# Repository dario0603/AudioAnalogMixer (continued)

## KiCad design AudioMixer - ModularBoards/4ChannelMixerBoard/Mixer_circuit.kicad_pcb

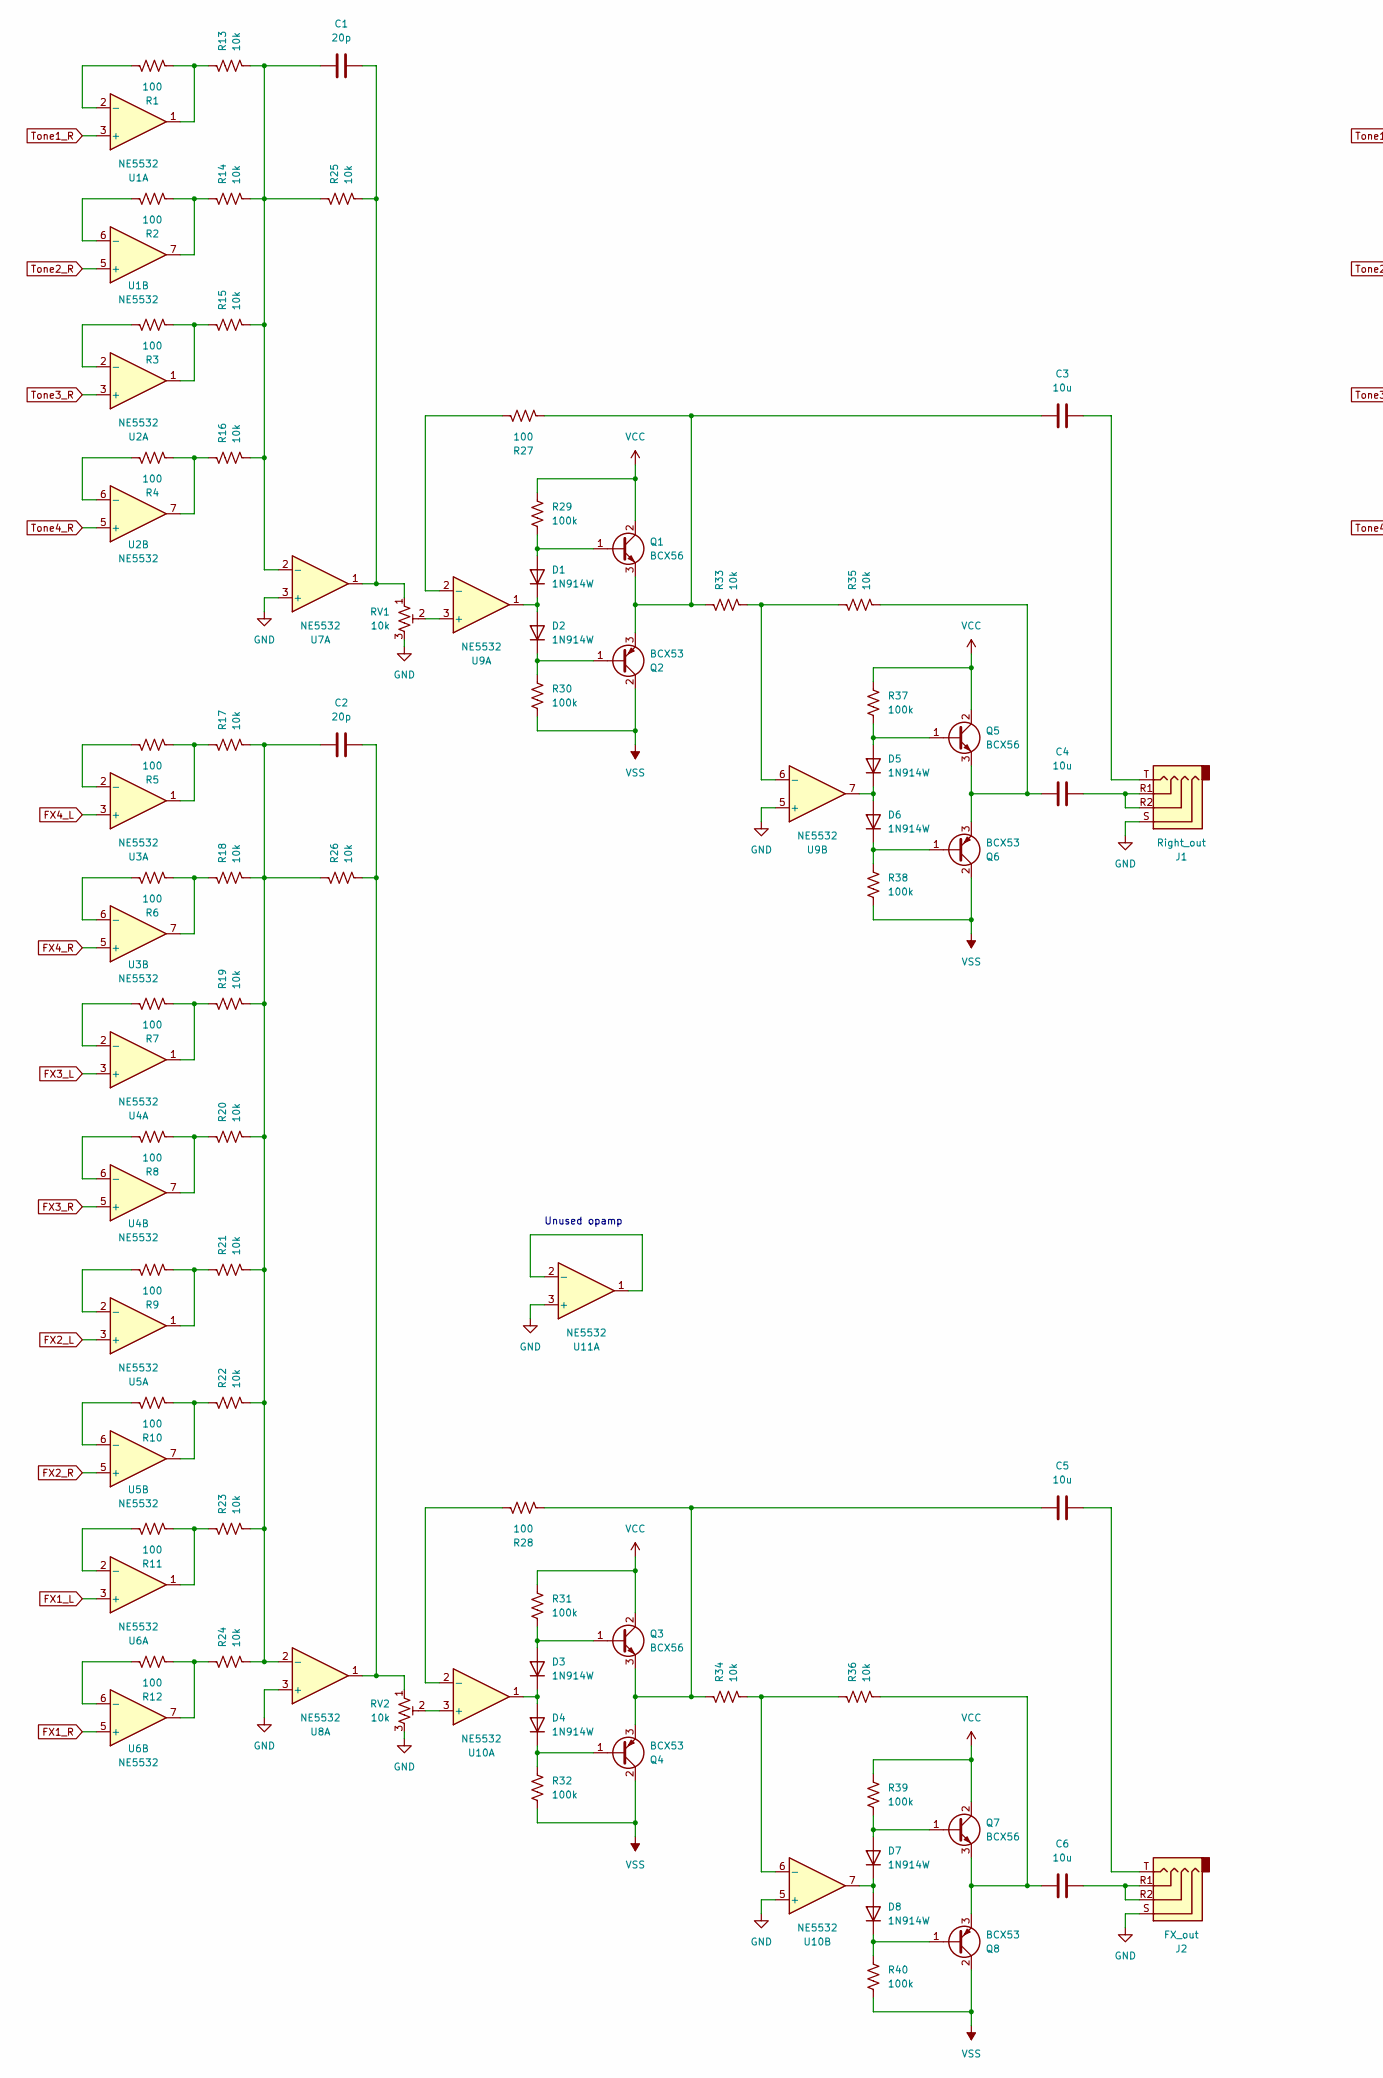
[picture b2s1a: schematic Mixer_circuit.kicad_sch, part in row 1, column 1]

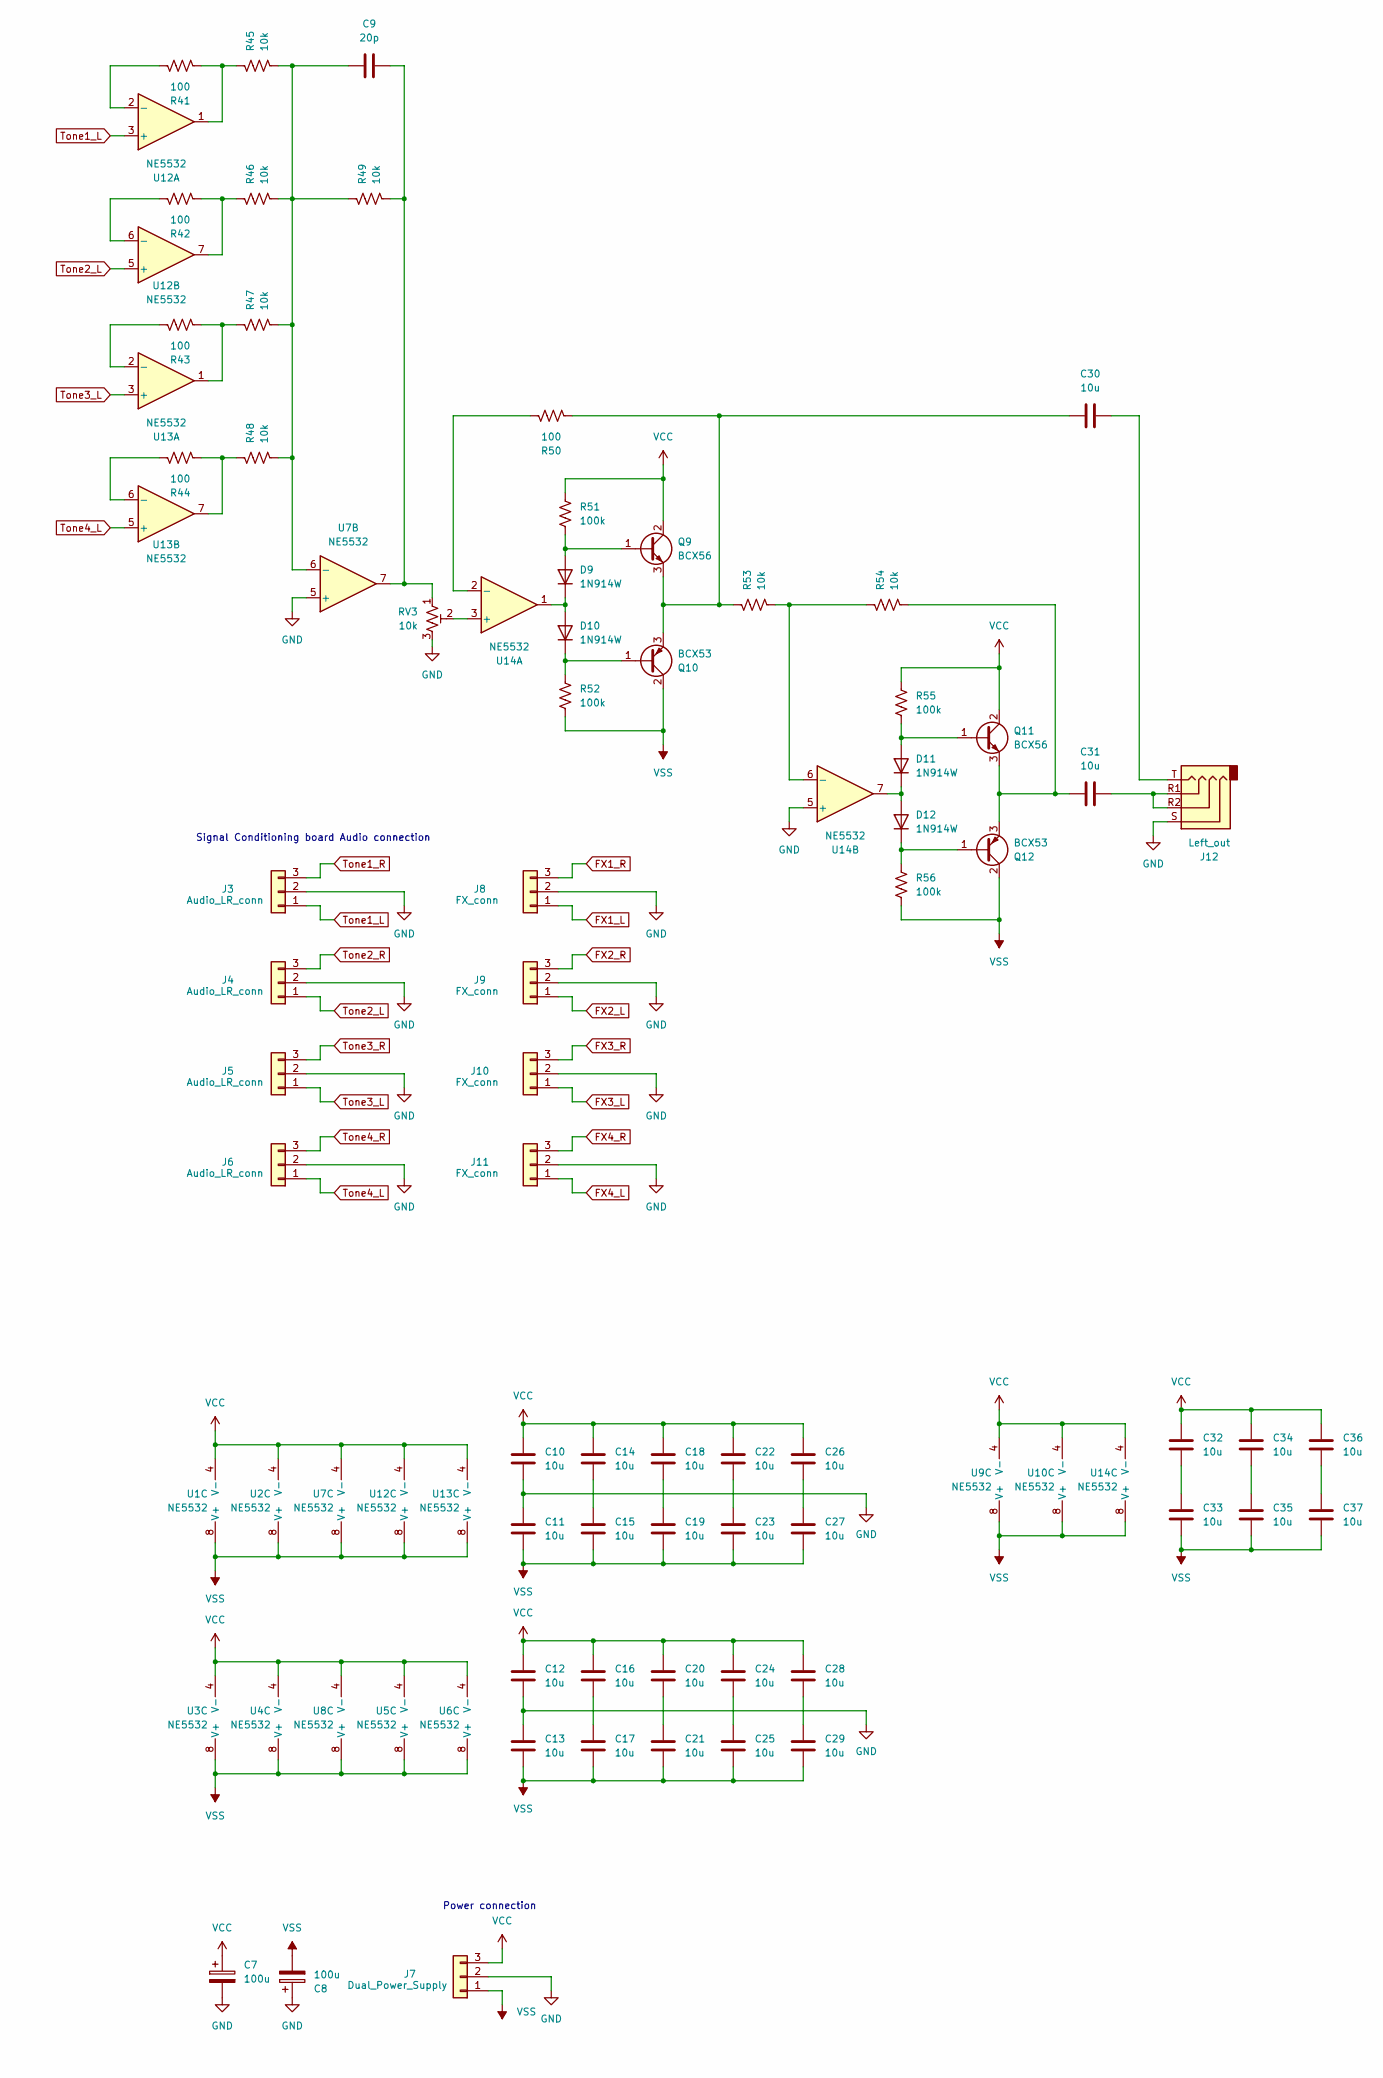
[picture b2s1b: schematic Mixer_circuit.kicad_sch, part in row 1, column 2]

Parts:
C1, C2, C9: 20p; C_0603_1608Metric_Pad1.08x0.95mm_HandSolder
C3, C4, C5, C6, C10, C11, C12, C13, C14, C15, C16, C17, C18, C19, C20, C21, C22, C23, C24, C25, C26, C27, C28, C29, C30, C31, C32, C33, C34, C35, C36, C37: 10u; C_1206_3216Metric_Pad1.33x1.80mm_HandSolder
C7, C8: 100u; CP_Elec_10x10.5
D1, D2, D3, D4, D5, D6, D7, D8, D9, D10, D11, D12: 1N914W; D_SOD-123
J1: Right_out; Jack_3.5mm_PJ320E_Horizontal
J2: FX_out; Jack_3.5mm_PJ320E_Horizontal
J3, J4, J5, J6: Audio_LR_conn; PinHeader_1x03_P2.54mm_Vertical
J7: Dual_Power_Supply; PinHeader_1x03_P2.54mm_Vertical
J8, J9, J10, J11: FX_conn; PinHeader_1x03_P2.54mm_Vertical
J12: Left_out; Jack_3.5mm_PJ320E_Horizontal
Q1, Q3, Q5, Q7, Q9, Q11: BCX56; SOT-89-3
Q2, Q4, Q6, Q8, Q10, Q12: BCX53; SOT-89-3
R1, R2, R3, R4, R5, R6, R7, R8, R9, R10, R11, R12, R27, R28, R41, R42, R43, R44, R50: 100; R_0603_1608Metric_Pad0.98x0.95mm_HandSolder
R13, R14, R15, R16, R17, R18, R19, R20, R21, R22, R23, R24, R25, R26, R33, R34, R35, R36, R45, R46, R47, R48, R49, R53, R54: 10k; R_0603_1608Metric_Pad0.98x0.95mm_HandSolder
R29, R30, R31, R32, R37, R38, R39, R40, R51, R52, R55, R56: 100k; R_0603_1608Metric_Pad0.98x0.95mm_HandSolder
RV1, RV2, RV3: 10k; Potentiometer_Alps_RK097_Single_Horizontal
U1, U2, U3, U4, U5, U6, U7, U8, U9, U10, U11, U12, U13, U14: NE5532; SOIC-8_3.9x4.9mm_P1.27mm

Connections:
FX1_L: J8.1, U6.3 (+)
FX1_R: J8.3, U6.5 (+)
FX2_L: J9.1, U5.3 (+)
FX2_R: J9.3, U5.5 (+)
FX3_L: J10.1, U4.3 (+)
FX3_R: J10.3, U4.5 (+)
FX4_L: J11.1, U3.3 (+)
FX4_R: J11.3, U3.5 (+)
GND: C7.2, C8.1, C10.1, C11.2, C12.1, C13.2, J1.S, J2.S, J3.2, J4.2, J5.2, J6.2, J7.2, J8.2, J9.2, J10.2, J11.2, J12.S, RV1.3, RV2.3, RV3.3, U7.3 (+), U7.5 (+), U8.3 (+), U9.5 (+), U10.5 (+), U11.3 (+), U14.5 (+)
unnamed: C1.2, R25.2, RV1.1, U7.1
unnamed: C2.2, R26.2, RV2.1, U8.1
unnamed: C3.2, J1.T
unnamed: C4.2, J1.R1, J1.R2
unnamed: C5.2, J2.T
unnamed: C6.2, J2.R1, J2.R2
unnamed: C9.2, R49.2, RV3.1, U7.7
unnamed: C14.1, C15.2
unnamed: C16.1, C17.2
unnamed: C18.1, C19.2
unnamed: C20.1, C21.2
unnamed: C22.1, C23.2
unnamed: C24.1, C25.2
unnamed: C26.1, C27.2
unnamed: C28.1, C29.2
unnamed: C30.2, J12.T
unnamed: C31.2, J12.R1, J12.R2
unnamed: C32.1, C33.2
unnamed: C34.1, C35.2
unnamed: C36.1, C37.2
unnamed: D1.2 (A), Q1.1 (B), R29.2
unnamed: D1.1 (K), D2.2 (A), U9.1
unnamed: D2.1 (K), Q2.1 (B), R30.1
unnamed: D3.2 (A), Q3.1 (B), R31.2
unnamed: D3.1 (K), D4.2 (A), U10.1
unnamed: D4.1 (K), Q4.1 (B), R32.1
unnamed: D5.2 (A), Q5.1 (B), R37.2
unnamed: D5.1 (K), D6.2 (A), U9.7
unnamed: D6.1 (K), Q6.1 (B), R38.1
unnamed: D7.2 (A), Q7.1 (B), R39.2
unnamed: D7.1 (K), D8.2 (A), U10.7
unnamed: D8.1 (K), Q8.1 (B), R40.1
unnamed: D9.2 (A), Q9.1 (B), R51.2
unnamed: D9.1 (K), D10.2 (A), U14.1
unnamed: D10.1 (K), Q10.1 (B), R52.1
unnamed: D11.2 (A), Q11.1 (B), R55.2
unnamed: D11.1 (K), D12.2 (A), U14.7
unnamed: D12.1 (K), Q12.1 (B), R56.1
unnamed: C3.1, Q1.3 (E), Q2.3 (E), R27.2, R33.1
unnamed: C5.1, Q3.3 (E), Q4.3 (E), R28.2, R34.1
unnamed: C4.1, Q5.3 (E), Q6.3 (E), R35.2
unnamed: C6.1, Q7.3 (E), Q8.3 (E), R36.2
unnamed: C30.1, Q9.3 (E), Q10.3 (E), R50.2, R53.1
unnamed: C31.1, Q11.3 (E), Q12.3 (E), R54.2
unnamed: R1.2, R13.1, U1.1
unnamed: R10.2, R22.1, U5.7
unnamed: R11.2, R23.1, U6.1
unnamed: R12.2, R24.1, U6.7
unnamed: R2.2, R14.1, U1.7
unnamed: R3.2, R15.1, U2.1
unnamed: R4.2, R16.1, U2.7
unnamed: R5.2, R17.1, U3.1
unnamed: R6.2, R18.1, U3.7
unnamed: R7.2, R19.1, U4.1
unnamed: R8.2, R20.1, U4.7
unnamed: R9.2, R21.1, U5.1
unnamed: R41.2, R45.1, U12.1
unnamed: R42.2, R46.1, U12.7
unnamed: R43.2, R47.1, U13.1
unnamed: R44.2, R48.1, U13.7
unnamed: R1.1, U1.2 (-)
unnamed: R2.1, U1.6 (-)
unnamed: R3.1, U2.2 (-)
unnamed: R4.1, U2.6 (-)
unnamed: R5.1, U3.2 (-)
unnamed: R6.1, U3.6 (-)
unnamed: R7.1, U4.2 (-)
unnamed: R8.1, U4.6 (-)
unnamed: R9.1, U5.2 (-)
unnamed: R10.1, U5.6 (-)
unnamed: R11.1, U6.2 (-)
unnamed: R12.1, U6.6 (-)
unnamed: C1.1, R13.2, R14.2, R15.2, R16.2, R25.1, U7.2 (-)
unnamed: C9.1, R45.2, R46.2, R47.2, R48.2, R49.1, U7.6 (-)
unnamed: C2.1, R17.2, R18.2, R19.2, R20.2, R21.2, R22.2, R23.2, R24.2, R26.1, U8.2 (-)
unnamed: RV1.2, U9.3 (+)
unnamed: R27.1, U9.2 (-)
unnamed: R33.2, R35.1, U9.6 (-)
unnamed: RV2.2, U10.3 (+)
unnamed: R28.1, U10.2 (-)
unnamed: R34.2, R36.1, U10.6 (-)
unnamed: U11.1, U11.2 (-)
unnamed: R41.1, U12.2 (-)
unnamed: R42.1, U12.6 (-)
unnamed: R43.1, U13.2 (-)
unnamed: R44.1, U13.6 (-)
unnamed: RV3.2, U14.3 (+)
unnamed: R50.1, U14.2 (-)
unnamed: R53.2, R54.1, U14.6 (-)
Tone1_L: J3.1, U12.3 (+)
Tone1_R: J3.3, U1.3 (+)
Tone2_L: J4.1, U12.5 (+)
Tone2_R: J4.3, U1.5 (+)
Tone3_L: J5.1, U13.3 (+)
Tone3_R: J5.3, U2.3 (+)
Tone4_L: J6.1, U13.5 (+)
Tone4_R: J6.3, U2.5 (+)
VCC: C7.1, C10.2, C12.2, C14.2, C16.2, C18.2, C20.2, C22.2, C24.2, C26.2, C28.2, C32.2, C34.2, C36.2, J7.3, Q1.2 (C), Q3.2 (C), Q5.2 (C), Q7.2 (C), Q9.2 (C), Q11.2 (C), R29.1, R31.1, R37.1, R39.1, R51.1, R55.1, U1.4 (V-), U2.4 (V-), U3.4 (V-), U4.4 (V-), U5.4 (V-), U6.4 (V-), U7.4 (V-), U8.4 (V-), U9.4 (V-), U10.4 (V-), U12.4 (V-), U13.4 (V-), U14.4 (V-)
VSS: C8.2, C11.1, C13.1, C15.1, C17.1, C19.1, C21.1, C23.1, C25.1, C27.1, C29.1, C33.1, C35.1, C37.1, J7.1, Q2.2 (C), Q4.2 (C), Q6.2 (C), Q8.2 (C), Q10.2 (C), Q12.2 (C), R30.2, R32.2, R38.2, R40.2, R52.2, R56.2, U1.8 (V+), U2.8 (V+), U3.8 (V+), U4.8 (V+), U5.8 (V+), U6.8 (V+), U7.8 (V+), U8.8 (V+), U9.8 (V+), U10.8 (V+), U12.8 (V+), U13.8 (V+), U14.8 (V+)

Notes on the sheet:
Power connection
Signal Conditioning board Audio connection
Unused opamp

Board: 2 copper layers, 146 parts (0 on the bottom side), 105 nets, no tracks yet.

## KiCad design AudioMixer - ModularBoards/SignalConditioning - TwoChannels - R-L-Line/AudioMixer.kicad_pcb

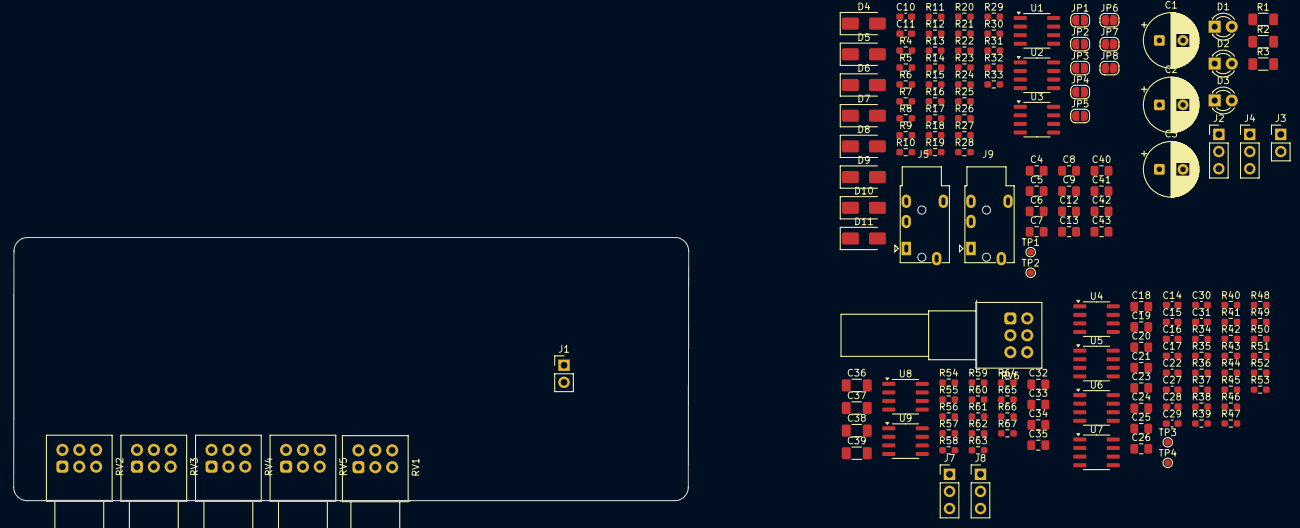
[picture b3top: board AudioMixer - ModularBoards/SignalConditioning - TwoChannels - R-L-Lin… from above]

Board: 2 copper layers, 156 parts (0 on the bottom side), 97 nets, no tracks yet.

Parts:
C1, C2, C3: 100u; CP_Radial_D8.0mm_P3.50mm
C4, C5, C6, C7, C8, C9, C18, C19, C20, C21, C23, C24, C25, C26, C32, C33, C34, C35: 10u; C_0805_2012Metric_Pad1.18x1.45mm_HandSolder
C10, C11: 1n; C_0603_1608Metric_Pad1.08x0.95mm_HandSolder
C12, C13, C40, C41, C42, C43: 22u; C_0805_2012Metric_Pad1.18x1.45mm_HandSolder
C14, C27: 4n7; C_0603_1608Metric_Pad1.08x0.95mm_HandSolder
C15, C28: 40n; C_0603_1608Metric_Pad1.08x0.95mm_HandSolder
C16, C29: 5n; C_0603_1608Metric_Pad1.08x0.95mm_HandSolder
C17, C30: 51n; C_0603_1608Metric_Pad1.08x0.95mm_HandSolder
C22, C31: 20p; C_0603_1608Metric_Pad1.08x0.95mm_HandSolder
C36, C37, C38, C39: 10u; C_1206_3216Metric_Pad1.33x1.80mm_HandSolder
D1, D2, D3: LED; LED_D3.0mm
D4, D5, D6, D7, D8, D9, D10, D11: 1SMA4740A; D_SMA
J1, J3: 48V_Phantom_Supply; PinHeader_1x02_P2.54mm_Vertical
J2, J4: Dual_Power_Supply; PinHeader_1x03_P2.54mm_Vertical
J5: Left_in; Jack_3.5mm_PJ320E_Horizontal
J7: Audio_connector; PinHeader_1x03_P2.54mm_Vertical
J8: FX_connector; PinHeader_1x03_P2.54mm_Vertical
J9: Right_in; Jack_3.5mm_PJ320E_Horizontal
JP1, JP4, JP5, JP8: Phase_0; SolderJumper-2_P1.3mm_Open_RoundedPad1.0x1.5mm
JP2, JP3, JP6, JP7: Phase_90; SolderJumper-2_P1.3mm_Open_RoundedPad1.0x1.5mm
R1, R2: 2.2k; R_1206_3216Metric_Pad1.30x1.75mm_HandSolder
R3: 6.8k; R_1206_3216Metric_Pad1.30x1.75mm_HandSolder
R4, R5: 100k; R_0603_1608Metric_Pad0.98x0.95mm_HandSolder
R6, R7, R8, R9: 2k2; R_0603_1608Metric_Pad0.98x0.95mm_HandSolder
R10, R11, R12, R13: 220; R_0603_1608Metric_Pad0.98x0.95mm_HandSolder
R14, R15, R16, R17, R18, R19, R20, R21, R22, R23, R24, R25, R26, R27, R28, R29, R30, R31, R32, R33, R34, R35, R36, R40, R41, R42, R44, R45, R46, R50, R51, R52, R56, R57, R62, R63, R66, R67: 10k; R_0603_1608Metric_Pad0.98x0.95mm_HandSolder
R37, R38, R39, R47, R48, R49, R58, R59, R64, R65: 100; R_0603_1608Metric_Pad0.98x0.95mm_HandSolder
R43, R53: 20k; R_0603_1608Metric_Pad0.98x0.95mm_HandSolder
R54, R55, R60, R61: 1k; R_0603_1608Metric_Pad0.98x0.95mm_HandSolder
RV1, RV2, RV3, RV4, RV5, RV6: 10k; Potentiometer_Alps_RK097_Dual_Horizontal
TP1, TP2: Tone; TestPoint_Pad_D1.0mm
TP3, TP4: FilteredWave; TestPoint_Pad_D1.0mm
U1, U2, U3, U4, U5, U6, U7, U8, U9: NE5532; SOIC-8_3.9x4.9mm_P1.27mm

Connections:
+48V: C1.1, J1.2, J3.2, R3.2
Eq_out_L: C31.2, R53.2, RV4.4, TP4.1, U7.1, U9.3 (+)
Eq_out_R: C22.2, R43.2, RV4.1, TP3.1, U5.1, U9.5 (+)
FX_L: J8.1, RV6.5
FX_R: J8.3, RV6.2
GND: C1.2, C2.2, C3.1, C4.2, C5.1, C6.2, C7.1, C8.2, C9.1, C18.2, C19.1, C20.2, C21.1, C23.2, C24.1, C25.2, C26.1, C32.2, C33.1, C34.2, C35.1, D1.1 (K), D2.2 (A), D3.1 (K), D4.2 (A), D5.2 (A), D6.2 (A), D7.2 (A), J1.1, J2.2, J3.1, J4.2, J5.S, J7.2, J8.2, J9.S, R4.2, R5.2, R30.1, R31.1, R54.2, R55.2, R60.2, R61.2, RV4.3, RV4.6, RV5.3, RV5.4, RV6.3, RV6.6, U4.3 (+), U4.5 (+), U5.3 (+), U5.5 (+), U6.3 (+), U6.5 (+), U7.3 (+), U7.5 (+)
unnamed: C12.1, R32.1, U3.7
unnamed: C13.1, R33.1, U3.1
unnamed: C14.2, R34.1
unnamed: C15.2, R35.1
unnamed: C16.1, R38.1, R41.2, RV2.2, RV2.3
unnamed: C17.1, R39.1, R42.2, RV3.2, RV3.3
unnamed: C27.2, R44.1
unnamed: C28.2, R45.1
unnamed: C29.1, R48.1, R51.2, RV2.5, RV2.6
unnamed: C30.1, R49.1, R52.2, RV3.5, RV3.6
unnamed: C36.1, R56.1, R58.1
unnamed: C36.2, RV5.1
unnamed: C37.1, R57.1, R59.1
unnamed: C37.2, RV5.6
unnamed: C38.1, R62.1, R64.1
unnamed: C38.2, R66.2
unnamed: C39.1, R63.1, R65.1
unnamed: C39.2, R67.2
unnamed: C40.1, J9.T
unnamed: C42.1, J5.T
unnamed: D1.2 (A), R1.1
unnamed: D2.1 (K), R2.1
unnamed: D3.2 (A), R3.1
unnamed: D4.1 (K), D8.1 (K)
unnamed: D5.1 (K), D9.1 (K)
unnamed: C40.2, D8.2 (A), JP1.1 (A), JP2.1 (A)
unnamed: C41.2, D9.2 (A), JP3.1 (A), JP4.1 (A)
unnamed: C42.2, D10.2 (A), JP5.1 (A), JP6.1 (A)
unnamed: D6.1 (K), D10.1 (K)
unnamed: C43.2, D11.2 (A), JP7.1 (A), JP8.1 (A)
unnamed: D7.1 (K), D11.1 (K)
unnamed: JP1.2 (B), JP3.2 (B), R6.1, R10.2
unnamed: JP2.2 (B), JP4.2 (B), R7.2, R11.2
unnamed: JP5.2 (B), JP7.2 (B), R8.1, R12.2
unnamed: JP6.2 (B), JP8.2 (B), R9.2, R13.2
unnamed: R4.1, R6.2, R7.1
unnamed: R5.1, R8.2, R9.1
unnamed: R14.2, R15.1
unnamed: R16.2, R17.1
unnamed: R18.1, R22.2, U2.1
unnamed: R19.1, R23.2, U2.7
unnamed: R20.1, R24.2, U1.1
unnamed: R21.1, R25.2, U1.7
unnamed: R22.1, R26.2
unnamed: R23.1, R27.2
unnamed: R24.1, R28.2
unnamed: R25.1, R29.2
unnamed: R37.1, R40.2, RV1.2, RV1.3
unnamed: R37.2, U4.1
unnamed: R38.2, U4.7
unnamed: R39.2, U5.7
unnamed: R47.1, R50.2, RV1.5, RV1.6
unnamed: R47.2, U6.1
unnamed: R48.2, U6.7
unnamed: R49.2, U7.7
unnamed: R58.2, U8.7
unnamed: R59.2, U8.1
unnamed: R64.2, U9.7
unnamed: R65.2, U9.1
unnamed: R66.1, RV6.1
unnamed: R67.1, RV6.4
unnamed: C11.1, R12.1, U1.3 (+)
unnamed: R16.1, R20.2, U1.2 (-)
unnamed: C11.2, R13.1, U1.5 (+)
unnamed: R17.2, R21.2, U1.6 (-)
unnamed: C10.1, R10.1, U2.3 (+)
unnamed: R14.1, R18.2, U2.2 (-)
unnamed: C10.2, R11.1, U2.5 (+)
unnamed: R15.2, R19.2, U2.6 (-)
unnamed: R28.1, R31.2, U3.3 (+)
unnamed: R29.1, R33.2, U3.2 (-)
unnamed: R26.1, R30.2, U3.5 (+)
unnamed: R27.1, R32.2, U3.6 (-)
unnamed: C14.1, RV1.1, U4.2 (-)
unnamed: C15.1, C16.2, RV2.1, U4.6 (-)
unnamed: C22.1, R40.1, R41.1, R42.1, R43.1, U5.2 (-)
unnamed: C17.2, R36.1, RV3.1, U5.6 (-)
unnamed: C27.1, RV1.4, U6.2 (-)
unnamed: C28.1, C29.2, RV2.4, U6.6 (-)
unnamed: C31.1, R50.1, R51.1, R52.1, R53.1, U7.2 (-)
unnamed: C30.2, R46.1, RV3.4, U7.6 (-)
unnamed: RV4.5, U8.3 (+)
unnamed: R55.1, R57.2, U8.2 (-)
unnamed: RV4.2, U8.5 (+)
unnamed: R54.1, R56.2, U8.6 (-)
unnamed: R61.1, R63.2, U9.2 (-)
unnamed: R60.1, R62.2, U9.6 (-)
Tone_L: C13.2, J7.1, R44.2, R45.2, R46.2, RV5.5, TP2.1
Tone_R: C12.2, J7.3, R34.2, R35.2, R36.2, RV5.2, TP1.1
VCC: C2.1, C4.1, C6.1, C8.1, C18.1, C20.1, C23.1, C25.1, C32.1, C34.1, J2.3, J4.3, R1.2, U1.8 (V+), U2.8 (V+), U3.8 (V+), U4.8 (V+), U5.8 (V+), U6.8 (V+), U7.8 (V+), U8.8 (V+), U9.8 (V+)
VSS: C3.2, C5.2, C7.2, C9.2, C19.2, C21.2, C24.2, C26.2, C33.2, C35.2, J2.1, J4.1, R2.2, U1.4 (V-), U2.4 (V-), U3.4 (V-), U4.4 (V-), U5.4 (V-), U6.4 (V-), U7.4 (V-), U8.4 (V-), U9.4 (V-)
